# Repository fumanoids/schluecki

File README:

README FOR THE SCHLUECKI HARD- AND SOFTWARE RELEASE
            ===================================================

          2014-02-13 FUmanoids' Schluecki Hardware Release v2014

          Copyright (c) 2014 FUmanoids / Freie Universität Berlin
                            All rights reserved

        For full license information, please refer to file LICENCE

Links:
       FUmanoids Homepage                           http://www.fumanoids.de
       FUmanoids on Facebook              http://www.facebook.com/fumanoids
       FUmanoids on Twitter                    http://twitter.com/fumanoids

       RoboCup Homepage                              http://www.robocup.org
       RoboCup Humanoid League Homepage          http://www.tzi.de/humanoid

This is part of the code/hardware release of team FUmanoids, version 2014. 

Our goal by releasing the source code and CAD files of components of our robot
is to provide some insight in humanoid soccer robot development, allowing other
teams to learn from our code and possibly our mistakes, but also to hopefully
encourage them to do the same and release their code as well. Though RoboCup is
a competition, it's also about research and finally to achieve our common goal -
to win against FIFA in 2050 ...

 1. PROJECT STRUCTURE
----------------------

The FUmanoids team has developed several software applications as well as our
own robots. The latter was developed internally and equipped with both
commercially available and self-built electronics.

This release addresses only the custom-built overvoltage suppressing board 
(named Schluecki) used in the FUmanoid robots.

This project consists solely of CAD files, a partlist and an assembly guide.

 1.1 Overview of the package
-----------------------------

The project's root directory is "schluecki" (the board's name).

The directories in the root directory are:

 - hardware -- Here you can find the CAD files for the PCB.

 2. THE SCHLUECKI PROJECT
------------------------- 

Over the years we have experienced serious issues with the robot's cabling.
At some point the isolation of some wires get damaged leading to a touching
of the supply voltage wire and a data wire. The resulting overvoltage 
might damage ICs connected to the data bus. In order to prevent damage
the Schluecki board provides means to attach big TVS Diodes to the robots
acting as a crowbar circuit in case of an overvoltage event. 

The overvoltage can be detected externally and counteracting measures can
be taken into account. Have a look in the PowerBoard project for an example:
http://www.fumanoids.de/hardware/powerboard

!!!!! This board does not guarantee any safety or robustness!            !!!!!
!!!!! Consider this board more like a way to reduce the risk of damages. !!!!!

 2.1 Hardware
-------------

To view the schematics and layout of this project we recommend using "CadSoft
EAGLE" which can be found at: http://www.cadsoftusa.com/

 2.2 Manufacturing
------------------

The PCB can be manufactured by most commonly known PCB services. A partlist can
be found in the folder where the schematics reside. But please double check the 
partlist since we cannot guarantee its completeness.

We chose every component on the board to be manually solderable. All you need is
a steady hand.

 3. CONTACT
-----------

We'd love to receive feedback, please feel free to contact us by email
at info@fumanoids.de. For information about our team and ongoing progress,
follow us on https://www.facebook.com/fumanoids, https://twitter.com/fumanoids
and http://www.fumanoids.de.

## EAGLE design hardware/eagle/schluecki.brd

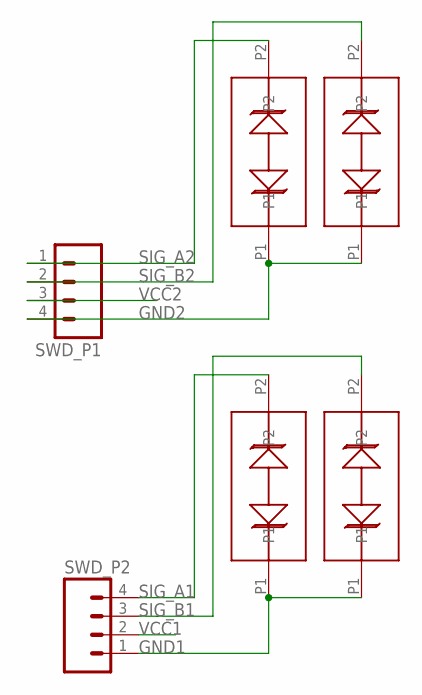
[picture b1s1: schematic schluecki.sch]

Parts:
SWD_P1, SWD_P2: M04; 04P
U$1, U$2, U$3, U$4: SMB/DO-214AA; DO-214AA

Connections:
GND1: SWD_P2.1, U$1.P1, U$2.P1
GND2: SWD_P1.4, U$3.P1, U$4.P1
SIG_A1: SWD_P2.4, U$1.P2
SIG_A2: SWD_P1.1, U$3.P2
SIG_B1: SWD_P2.3, U$2.P2
SIG_B2: SWD_P1.2, U$4.P2
VCC1: SWD_P2.2
VCC2: SWD_P1.3

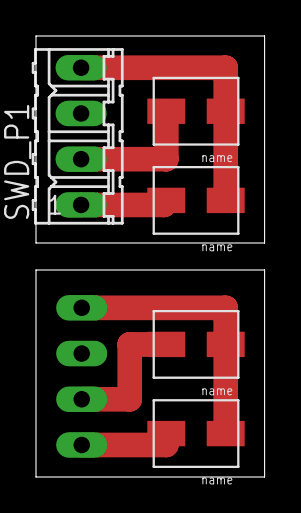
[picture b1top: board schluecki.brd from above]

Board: 2 copper layers, 12.7 x 24.5 mm, 6 parts (1 on the bottom side), 6 nets.

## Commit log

2014-02-13 code release 2014
